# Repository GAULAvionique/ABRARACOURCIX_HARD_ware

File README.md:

# PCB_CTRL_Surface
Le design du hardware qui assurera le contrôle de surface pour le drone prototype.

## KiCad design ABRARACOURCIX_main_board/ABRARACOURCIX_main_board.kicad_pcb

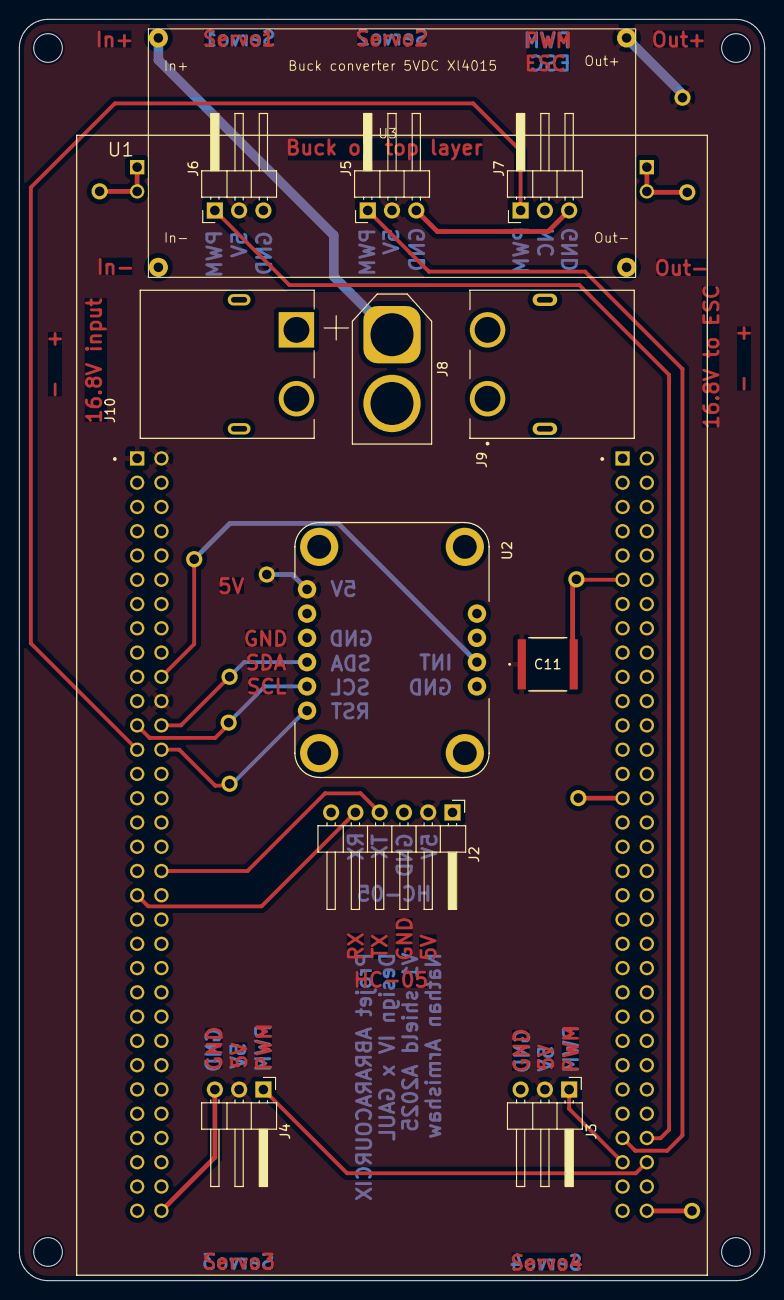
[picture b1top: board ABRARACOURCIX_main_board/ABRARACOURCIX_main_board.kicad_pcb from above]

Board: 2 copper layers, 78.0 x 132.0 mm, 13 parts (0 on the bottom side), 15 nets.

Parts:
C11: 10u; CAP_MU_15750_RUB-L
J2: Conn_01x06_Socket; PinHeader_1x06_P2.54mm_Horizontal
J3, J4, J5, J6, J7: Conn_01x03_Socket; PinHeader_1x03_P2.54mm_Horizontal
J8: XT60PW-M; AMASS_XT60-F_1x02_P7.20mm_Vertical
J9: XT60PW-F; AMASS_XT60PW-F
J10: XT60PW-M; AMASS_XT60PW-M
U1: STM32F429I-DISC1; MODULE_STM32F429I-DISC1
U2: BNO055_breakout; MODULE_2472
U3: Buck_breakout_Xl4015

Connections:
+5V: C11.1, J2.2, J3.2, J4.2, J5.2, J6.2, U1.P1_1 (5V), U1.P1_2 (5V), U1.P1_22 (VDD), U2.1 (VIN), U3.3 (Out+)
/Power/16V_post-switch: J8.1 (+), J9.2, U3.1 (In+)
/Power/16V_pre-switch: J8.2 (-), J10.1 (+)
BNO_Int: U1.P1_20 (PB9), U2.8 (INT)
BNO_Reset: U1.P1_26 (PB5), U2.6 (RST)
GND: C11.2, J2.3, J3.3, J4.3, J5.3, J6.3, J7.3, J9.1, J9.S1 (SHIELD), J9.S2 (SHIELD), J10.2 (-), U1.JP1_1 (GND_1), U1.JP1_2 (GND_1), U1.JP2_1 (GND_2), U1.JP2_2 (GND_2), U1.P1_63 (GND_1), U1.P1_64 (GND_1), U1.P2_11 (GND_2), U1.P2_29 (GND_2), U1.P2_63 (GND_2), U1.P2_64 (GND_2), U2.3 (GND), U2.7 (ADR), U3.2 (In-), U3.4 (Out-)
HC_RX: J2.5, U1.P1_37 (PD5)
HC_TX: J2.4, U1.P1_36 (PD6)
PWM_Moteur: J7.1, U1.P1_25 (PB4)
PWM_Servo_1: J6.1, U1.P2_58 (PD12)
PWM_Servo_2: J5.1, U1.P2_57 (PD13)
PWM_Servo_3: J4.1, U1.P2_60 (PD14)
PWM_Servo_4: J3.1, U1.P2_59 (PD15)
SCL: U1.P1_23 (PB6), U2.5 (SCL)
SDA: U1.P1_24 (PB7), U2.4 (SDA)

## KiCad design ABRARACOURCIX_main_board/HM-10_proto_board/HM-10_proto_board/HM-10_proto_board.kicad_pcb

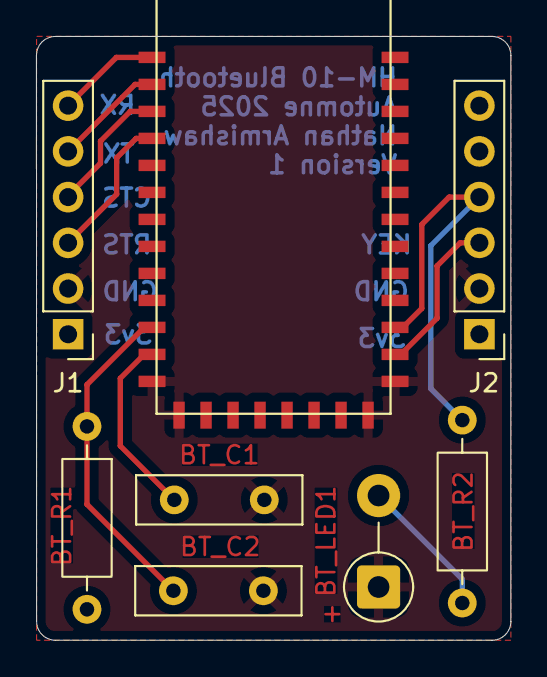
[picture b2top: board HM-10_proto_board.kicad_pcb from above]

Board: 2 copper layers, 26.4 x 33.5 mm, 8 parts (0 on the bottom side), 10 nets.

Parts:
BT_C1: 10uF; C_Disc_D9.0mm_W2.5mm_P5.00mm
BT_C2: 100nF; C_Disc_D9.0mm_W2.5mm_P5.00mm
BT_LED1: BLUE; D_DO-15_P5.08mm_Vertical_AnodeUp
BT_R1: 10k; R_Axial_DIN0207_L6.3mm_D2.5mm_P10.16mm_Horizontal
BT_R2: 1k5; R_Axial_DIN0207_L6.3mm_D2.5mm_P10.16mm_Horizontal
E2: HM-10
J1, J2: Conn_01x06_Socket; PinHeader_1x06_P2.54mm_Vertical

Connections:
+3V3: BT_C1.1, BT_R1.2, E2.12 (+3.3V), J1.1, J2.1
BT_Config/Run: E2.23 (KEY), J2.3
GND: BT_C1.2, BT_C2.2, BT_LED1.1 (K), E2.13 (GND), E2.14 (GND__1), E2.21 (GND__2), E2.22 (GND__3), J1.2, J2.2
unnamed: BT_LED1.2 (A), BT_R2.2
unnamed: BT_R2.1, E2.24 (LED), J2.4
unnamed: BT_C2.1, BT_R1.1, E2.11 (RESET)
UART2_BT_RX: E2.1 (UART_TX), J1.6
UART2_BT_TX: E2.2 (UART_RX), J1.5
UART_CTS: E2.3 (UART_CTS), J1.4
UART_RTS: E2.4 (UART_RTS), J1.3

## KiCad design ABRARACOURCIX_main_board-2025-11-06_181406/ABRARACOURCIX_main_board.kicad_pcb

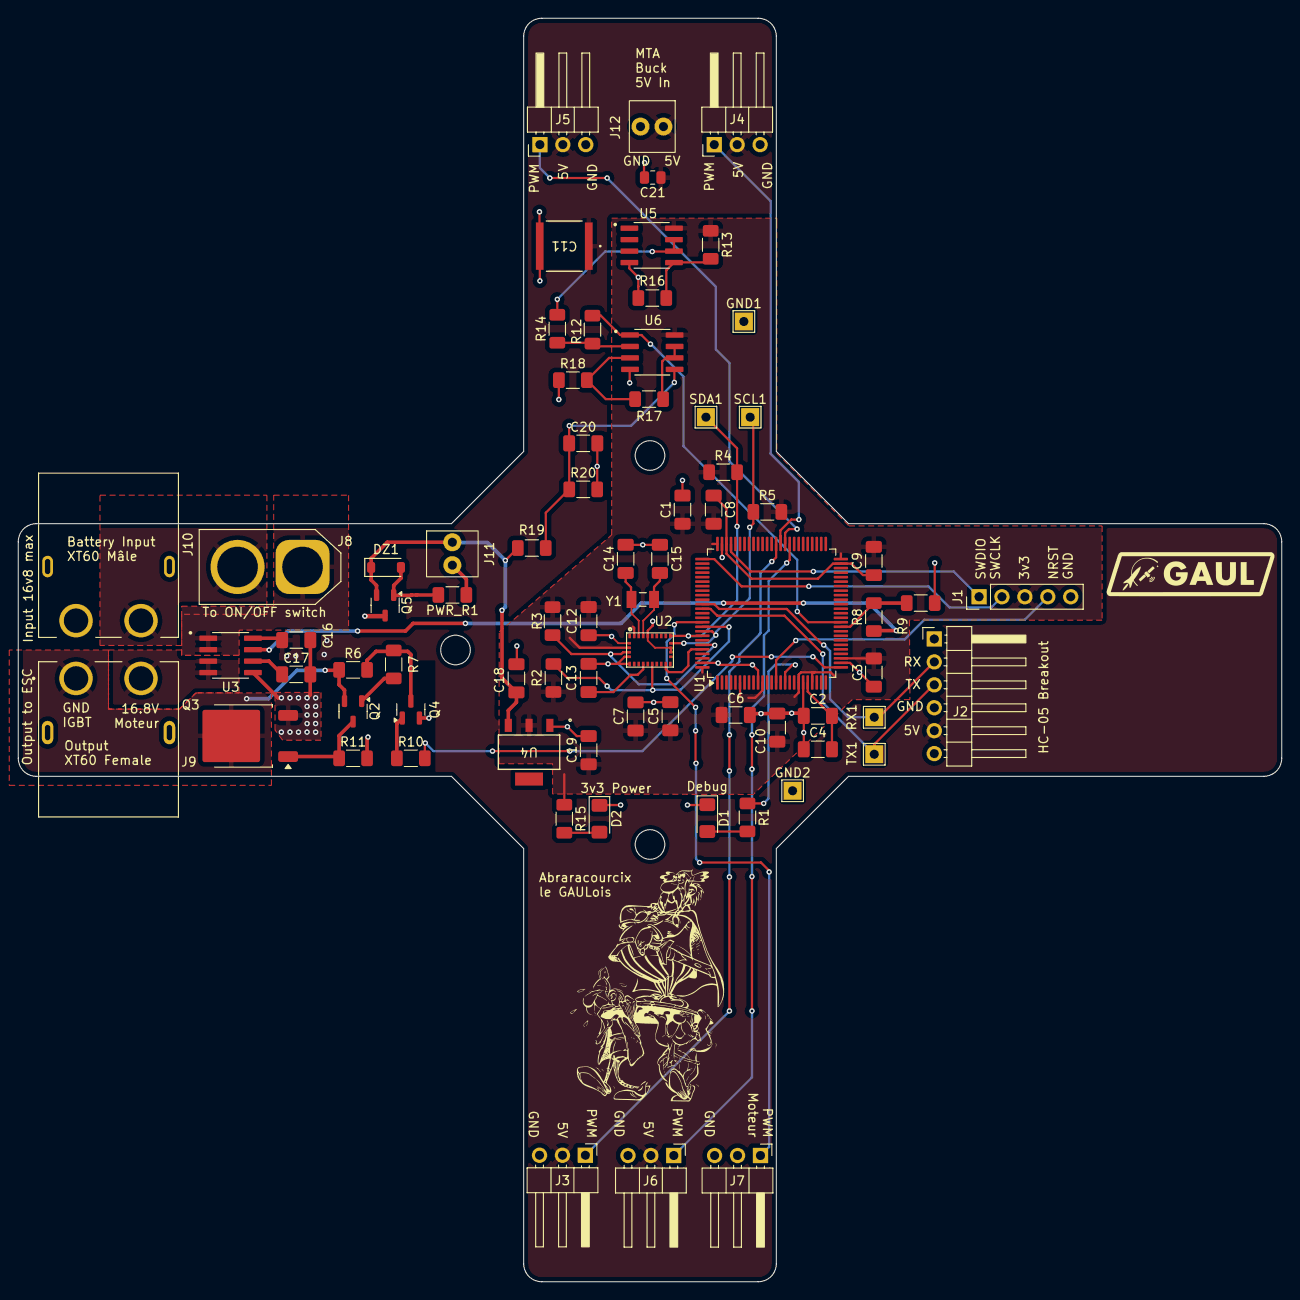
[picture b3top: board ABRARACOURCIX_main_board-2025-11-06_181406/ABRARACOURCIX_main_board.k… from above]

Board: 2 copper layers, 140.0 x 140.0 mm, 75 parts (0 on the bottom side), 47 nets.

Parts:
Abraracourcix_moyen: LOGO; Abraracourcix_moyen
C1, C2, C3, C5, C6: 100n; C_1206_3216Metric_Pad1.33x1.80mm_HandSolder
C4, C10, C20: 1u; C_1206_3216Metric_Pad1.33x1.80mm_HandSolder
C7: 4.7u; C_1206_3216Metric_Pad1.33x1.80mm_HandSolder
C8, C9: 2.2u; C_1206_3216Metric_Pad1.33x1.80mm_HandSolder
C11: 10u; CAP_MU_15750_RUB-L
C12: 100nF; C_1206_3216Metric_Pad1.33x1.80mm_HandSolder
C13: 1uF; C_1206_3216Metric_Pad1.33x1.80mm_HandSolder
C14, C15: 22pF; C_1206_3216Metric_Pad1.33x1.80mm_HandSolder
C16: 0.1u; C_1206_3216Metric_Pad1.33x1.80mm_HandSolder
C17: 1n; C_1206_3216Metric_Pad1.33x1.80mm_HandSolder
C18: 10u; C_1206_3216Metric_Pad1.33x1.80mm_HandSolder
C19: 22u; C_1206_3216Metric_Pad1.33x1.80mm_HandSolder
C21: 22u; R_0805_2012Metric
D1, D2: 599-0410-127F; D_1206_3216Metric_Pad1.42x1.75mm_HandSolder
DZ1: SZMMSZ4679T1G; D_SOD-123
GND1, GND2: TestPoint; TestPoint_THTPad_2.0x2.0mm_Drill1.0mm
J1: Conn_01x05_Socket; PinHeader_1x05_P2.54mm_Vertical
J2: Conn_01x06_Socket; PinHeader_1x06_P2.54mm_Horizontal
J3, J4, J5, J6, J7: Conn_01x03_Socket; PinHeader_1x03_P2.54mm_Horizontal
J8: XT60PW-M; AMASS_XT60-F_1x02_P7.20mm_Vertical
J9: XT60PW-F; AMASS_XT60PW-F
J10: XT60PW-M; AMASS_XT60PW-M
J11, J12: Conn_01x02_Pin; MTA_100_2pos
PWR_R1: 100k; R_1206_3216Metric_Pad1.30x1.75mm_HandSolder
Q2: DSS20200L-7-PNP; SOT-23-3
Q3: IKD15N60R; TO-252-2
Q4: NPN-DSS20201L-7; SOT-23
Q5: NTR4101PT1G; SOT-23-3
R1, R15: 40; R_1206_3216Metric_Pad1.30x1.75mm_HandSolder
R2, R3: 10K; R_1206_3216Metric_Pad1.30x1.75mm_HandSolder
R4: 1K; R_1206_3216Metric_Pad1.30x1.75mm_HandSolder
R5: 1k; R_1206_3216Metric_Pad1.30x1.75mm_HandSolder
R6, R8, R11, R13, R14, R17, R20: 10k; R_1206_3216Metric_Pad1.30x1.75mm_HandSolder
R7, R10: 1k5; R_1206_3216Metric_Pad1.30x1.75mm_HandSolder
R9: 20k; R_1206_3216Metric_Pad1.30x1.75mm_HandSolder
R12, R16, R18: 30k; R_1206_3216Metric_Pad1.30x1.75mm_HandSolder
R19: 40k; R_1206_3216Metric_Pad1.30x1.75mm_HandSolder
RX1: TestPoint; TestPoint_THTPad_2.0x2.0mm_Drill1.0mm
SCL1: TestPoint; TestPoint_THTPad_2.0x2.0mm_Drill1.0mm
SDA1: TestPoint; TestPoint_THTPad_2.0x2.0mm_Drill1.0mm
TX1: TestPoint; TestPoint_THTPad_2.0x2.0mm_Drill1.0mm
U1: STM32F429VITx; LQFP-100_14x14mm_P0.5mm
U2: BNO055; BNO055_LGA28R50P4X10_380X520X100
U3: Current_sens_ACS712ELCTR-20A-T; Current_sens_SOIC127P600X175-8N
U4: AZ1117CH-3.3TRG1; AZ1117CH_3_3TRG1-L
U5, U6: LMC6482AIMX/NOPB; SOIC127P599X175-8N
Y1: ABS07-32.768KHZ-T; XTAL_ABS07-32.768KHZ-T

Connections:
+3.3V: C1.1, C3.1, C5.1, C6.1, C7.1, C8.2, C9.2, C10.1, C12.2, C19.1, J1.3, R2.1, R3.1, R4.1, R5.2, R13.1, R15.1, U1.6 (VBAT), U1.11 (VDD), U1.19 (VDD), U1.22 (VDDA), U1.28 (VDD), U1.50 (VDD), U1.75 (VDD), U1.100 (VDD), U2.3 (VDD), U2.28 (VDDIO), U4.2 (OUTPUT), U5.8 (V+), U6.8 (V+)
+5V: C11.1, C16.1, C21.1, J2.5, J3.2, J4.2, J5.2, J6.2, J12.1, U3.8 (VCC)
/Power/16V_motor: J9.2, Q5.D, U3.3 (IP-__1), U3.4 (IP-)
/Power/16V_post-switch: J8.1 (+), U3.1 (IP+), U3.2 (IP+__1)
/Power/16V_pre-switch: J8.2 (-), J10.1 (+)
/Power/GND_IGBT: J9.1, Q2.E, Q3.C, R6.1
BNO_BOOT: R3.2, U1.95 (PB8), U2.4 (NBOOT_LOAD_PIN)
BNO_INT_OUT: U1.96 (PB9), U2.14 (INT)
BNO_RESET: R2.2, U1.91 (PB5), U2.11 (NRESET)
GND: C1.2, C2.1, C3.2, C4.1, C5.2, C6.2, C7.2, C10.2, C11.2, C12.1, C13.1, C14.2, C15.1, C16.2, C17.2, C18.2, C19.2, C20.2, C21.2, D1.1 (K), D2.1 (K), GND1.1, GND2.1, J1.5, J2.4, J3.3, J4.3, J5.3, J6.3, J7.3, J9.S1 (SHIELD), J9.S2 (SHIELD), J10.2 (-), J11.2, J12.2, PWR_R1.2, Q3.E, Q4.E, R9.2, R11.2, R16.2, R18.1, R20.2, U1.10 (VSS), U1.20 (VSSA), U1.27 (VSS), U1.74 (VSS), U1.99 (VSS), U2.2 (GND), U2.5 (PS1), U2.6 (PS0), U2.17 (COM3), U2.18 (COM2), U2.25 (GNDIO), U3.5 (GND), U4.1 (ADJ/GND), U5.4 (V-), U6.4 (V-)
HC_RX: J2.2, RX1.1, U1.86 (PD5)
HC_TX: J2.3, TX1.1, U1.87 (PD6)
Motor_switch: R10.2, U1.26 (PA3)
NRST: J1.4, U1.14 (NRST)
unnamed: D1.2 (A), R1.2
unnamed: D2.2 (A), R15.2
unnamed: DZ1.2 (A), PWR_R1.1, Q5.G
unnamed: Q2.B, R7.1
unnamed: Q2.C, Q3.G, R11.1
unnamed: Q4.B, R10.1
unnamed: Q4.C, R6.2, R7.2
unnamed: R1.1, U1.16 (PC1)
unnamed: C8.1, C9.1, U1.49 (VCAP_1), U1.73 (VCAP_2)
unnamed: C2.2, C4.2, U1.21 (VREF+)
unnamed: C13.2, U2.9 (CAP)
unnamed: C17.1, U3.6 (FILTER)
unnamed: R8.1, U3.7 (VIOUT)
unnamed: R13.2, R16.1, U5.5 (+)
unnamed: R14.1, U5.6 (-), U5.7
unnamed: R17.2, R18.2, U6.3 (+)
unnamed: R12.1, R14.2, U6.2 (-)
unnamed: C20.1, R19.2, R20.1, U6.5 (+)
unnamed: R17.1, U6.6 (-), U6.7
PWM_Moteur: J7.1, U1.90 (PB4)
PWM_Servo_1: J6.1, U1.59 (PD12)
PWM_Servo_2: J5.1, U1.60 (PD13)
PWM_Servo_3: J4.1, U1.61 (PD14)
PWM_Servo_4: J3.1, U1.62 (PD15)
SCL: R5.1, SCL1.1, U1.92 (PB6), U2.19 (COM1)
SDA: R4.2, SDA1.1, U1.93 (PB7), U2.20 (COM0)
SYS_SWCLK: J1.2, U1.76 (PA14)
SYS_SWDIO: J1.1, U1.72 (PA13)
VBAT_ADC: R12.2, U1.36 (PB1), U6.1
VBAT_sense: C18.1, DZ1.1 (K), J11.1, Q5.S, R19.1, U4.3 (INPUT)
VIout_sense: R8.2, R9.1, U1.35 (PB0)
XIN32: C14.1, U2.27 (XIN32), Y1.2
XOUT32: C15.2, U2.26 (XOUT32), Y1.1

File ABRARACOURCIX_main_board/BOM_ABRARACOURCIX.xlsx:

Reference | Quantity | Order quantity | Value | Footprint | Digikey link | Digikey part number | Description
C11 | 1 | 1 | 10u | Librairie_footprint:CAP_MU_15750_RUB-L | https://www.digikey.ca/en/products/detail/rubycon/16MU106MC4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 | 1189-2511-6-ND | Unpolarized film capacitor
C12 | 1 | 10 | 100nF | Capacitor_SMD:C_1206_3216Metric_Pad1.33x1.80mm_HandSolder | https://www.digikey.ca/en/products/detail/walsin-technology-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 | 1292-1605-1-ND | Unpolarized capacitor
C14, C15 | 2 | 10 | 22pF | Capacitor_SMD:C_1206_3216Metric_Pad1.33x1.80mm_HandSolder | https://www.digikey.ca/en/products/detail/kemet/C1206C220K1G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 | 399-C1206C220K1GACTUCT-ND | Unpolarized capacitor
C17 | 1 | 10 | 1n | Capacitor_SMD:C_1206_3216Metric_Pad1.33x1.80mm_HandSolder | https://www.digikey.ca/en/products/detail/walsin-technology-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 | 1292-1598-1-ND | Unpolarized capacitor
C18 | 1 | 10 | 10u | Capacitor_SMD:C_1206_3216Metric_Pad1.33x1.80mm_HandSolder | https://www.digikey.ca/en/products/detail/walsin-technology-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 | 1292-1206X106K250CT-ND | Unpolarized capacitor
C19, C21 | 2 | 10 | 22u | Capacitor_SMD:C_1206_3216Metric_Pad1.33x1.80mm_HandSolder | https://www.digikey.ca/en/products/detail/walsin-technology-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 | 1292-1206X226M160CT-ND | Unpolarized capacitor
C1-C3, C5, C6, C16 | 6 | 10 | 100n | Capacitor_SMD:C_1206_3216Metric_Pad1.33x1.80mm_HandSolder | Link | 1292-1605-1-ND | Unpolarized capacitor
C4, C10, C13, C20 | 4 | 10 | 1u | Capacitor_SMD:C_1206_3216Metric_Pad1.33x1.80mm_HandSolder | https://www.digikey.ca/en/products/detail/walsin-technology-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 | 1292-1206B105K250CT-ND | Unpolarized capacitor
C7 | 1 | 10 | 4.7u | Capacitor_SMD:C_1206_3216Metric_Pad1.33x1.80mm_HandSolder | https://www.digikey.ca/en/products/detail/walsin-technology-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 | 1292-1206B475K250CT-ND | Unpolarized capacitor
C8, C9 | 2 | 10 | 2.2u | Capacitor_SMD:C_1206_3216Metric_Pad1.33x1.80mm_HandSolder | https://www.digikey.ca/en/products/detail/walsin-technology-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 | 1292-1206B225K250CT-ND | Unpolarized capacitor
D1, D2 | 2 | 10 | 599-0410-127F | Diode_SMD:D_1206_3216Metric_Pad1.42x1.75mm_HandSolder | https://www.digikey.ca/en/products/detail/dialight/599-0410-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 | 350-599-0410-127FCT-ND | Light emitting diode
DZ1 | 1 | 10 | SZMMSZ4679T1G | Diode_SMD:D_SOD-123 | https://www.digikey.ca/en/products/detail/onsemi/SZMMSZ4679T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 | SZMMSZ4679T1GOSCT-ND | 18V, 500mW, 5%, Zener diode, MiniMELF
J1 | 1 | 2 | Conn_01x05_Socket | Connector_PinHeader_2.54mm:PinHeader_1x05_P2.54mm_Vertical | https://www.digikey.ca/en/products/detail/sullins-connector-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 | S5480-ND | CONN HDR 5POS 0.1 GOLD PCB R/A
J2 | 1 | 2 | Conn_01x06_Socket | Connector_PinHeader_2.54mm:PinHeader_1x06_P2.54mm_Horizontal | https://www.digikey.ca/en/products/detail/samtec-inc/SSW-106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 | SSW-106-03-F-S-RA-ND | Generic connector, single row, 01x06, script generated
J3-J7 | 5 | 5 | Conn_01x03_Socket | Connector_PinHeader_2.54mm:PinHeader_1x03_P2.54mm_Horizontal | https://www.digikey.ca/en/products/detail/harwin-inc/M20-996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 | M20-9960345 | Generic connector, single row, 01x03, script generated
PWR_R1 | 1 | 2 | 100k | Resistor_SMD:R_1206_3216Metric_Pad1.30x1.75mm_HandSolder | https://www.digikey.ca/en/products/detail/bourns-inc/CR1206-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 | CR1206-JW-104ELFCT-ND | RES SMD 100K OHM 5% 1/4W 1206
Q2 | 1 | 3 | DSS20200L-7-PNP | Package_TO_SOT_SMD:SOT-23-3 | https://www.digikey.ca/en/products/detail/diodes-incorporate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 | DSS20200LDICT-ND | Bipolar transistor symbol for simulation only, substrate tied to the emitter
Q3 | 1 | 2 | IKD15N60R | Package_TO_SOT_SMD:TO-252-2 | https://www.digikey.ca/en/products/detail/infineon-technolog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 | NTR4101PT1GOSCT-ND | N-IGBT transistor, collector/emitter/gate
Q4 | 1 | 3 | NPN-DSS20201L-7 | Package_TO_SOT_SMD:SOT-23 | https://www.digikey.ca/en/products/detail/diodes-incorporate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 | DSS20201LDICT-ND | Bipolar transistor symbol for simulation only, substrate tied to the emitter
Q5 | 1 | 3 | NTR4101PT1G | Package_TO_SOT_SMD:SOT-23-3 | https://www.digikey.ca/en/products/detail/onsemi/NTR4101PT1G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 | NTR4101PT1GOSCT-ND | P-MOSFET transistor, drain/source/gate
R1, R15 | 2 | 10 | 40.2 | Resistor_SMD:R_1206_3216Metric_Pad1.30x1.75mm_HandSolder | https://www.digikey.ca/en/products/detail/bourns-inc/CR1206-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 | 118-CR1206-FX-40R2ELFCT-ND | Resistor
R12, R16, R18 | 3 | 10 | 30k | Resistor_SMD:R_1206_3216Metric_Pad1.30x1.75mm_HandSolder | https://www.digikey.ca/en/products/detail/bourns-inc/CR1206-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 | 118-CR1206-JW-303ELFCT-ND | Resistor
R19 | 1 | 10 | 40.2k | Resistor_SMD:R_1206_3216Metric_Pad1.30x1.75mm_HandSolder | https://www.digikey.ca/en/products/detail/bourns-inc/CR1206-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 | 118-CR1206-FX-4022ELFCT-ND | Resistor
R2, R3 | 2 | 10 | 10K | Resistor_SMD:R_1206_3216Metric_Pad1.30x1.75mm_HandSolder | https://www.digikey.ca/en/products/detail/bourns-inc/CR1206-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 | CR1206-JW-103ELFCT-ND | Resistor
R4 | 1 | 10 | 1K | Resistor_SMD:R_1206_3216Metric_Pad1.30x1.75mm_HandSolder | https://www.digikey.ca/en/products/detail/bourns-inc/CR1206-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 | 118-CR1206-JW-102ELFCT-ND | Resistor
R5 | 1 | 10 | 1k | Resistor_SMD:R_1206_3216Metric_Pad1.30x1.75mm_HandSolder | https://www.digikey.ca/en/products/detail/bourns-inc/CR1206-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 | 118-CR1206-JW-102ELFCT-ND | Resistor
R6, R8, R11, R13, R14, R17, R20 | 7 | 10 | 10k | Resistor_SMD:R_1206_3216Metric_Pad1.30x1.75mm_HandSolder | https://www.digikey.ca/en/products/detail/bourns-inc/CR1206-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 | CR1206-JW-103ELFCT-ND | Resistor
R7, R10 | 2 | 10 | 1k5 | Resistor_SMD:R_1206_3216Metric_Pad1.30x1.75mm_HandSolder | https://www.digikey.ca/en/products/detail/bourns-inc/CR1206-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 | CR1206-JW-152ELFCT-ND | Resistor
R9 | 1 | 10 | 20k | Resistor_SMD:R_1206_3216Metric_Pad1.30x1.75mm_HandSolder | https://www.digikey.ca/en/products/detail/bourns-inc/CR1206-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 | 118-CR1206-JW-203ELFCT-ND | RES SMD 20K OHM 5% 1/4W 1206
U1 | 1 | 2 | STM32F429VITx | Package_QFP:LQFP-100_14x14mm_P0.5mm | https://www.digikey.ca/en/products/detail/stmicroelectronics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 | 497-14052-ND | STMicroelectronics Arm Cortex-M4 MCU, 2048KB flash, 256KB RAM, 180 MHz, 1.8-3.6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
U2 | 1 | 2 | BNO055 | Librairie_footprint:BNO055_LGA28R50P4X10_380X520X100 | https://www.digikey.ca/en/products/detail/bosch-sensortec/BN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 | 828-1058-1-ND | Inertial Measurement Unit
U3 | 1 | 2 | Current_sens_ACS712ELCTR-20A-T | Librairie_footprint:Current_sens_SOIC127P600X175-8N | https://www.digikey.ca/en/products/detail/allegro-microsyste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 | 620-1190-1-ND | CURRENT SENSOR HE/OL 20A 8-SOIC
U4 | 1 | 10 | AZ1117CH-3.3TRG1 | Librairie_footprint:AZ1117CH_3_3TRG1-L | https://www.digikey.ca/en/products/detail/diodes-incorporate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 | AZ1117CH-3.3TRG1DICT-ND | 3v3 LDO
U5, U6 | 2 | 2 | LMC6482AIMX/NOPB | Librairie_footprint:SOIC127P599X175-8N | https://www.digikey.ca/en/products/detail/texas-instruments/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 | LMC6482AIMX/NOPBCT-ND | IC CMOS 2 CIRCUIT 8SOIC
Y1 | 1 | 2 | ABS07-32.768KHZ-T | Librairie_footprint:XTAL_ABS07-32.768KHZ-T | https://www.digikey.ca/en/products/detail/abracon-llc/ABS07-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 | 535-9542-1-ND | CRYSTAL 32.7680KHZ 12.5PF SMD

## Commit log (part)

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2025-09-05 Création des docs
2025-09-05 schema bloc
2025-09-06 Update au schema bloc
2025-09-10 Importation des librairies
    Librairies des composantes principales
    Reste à ajouter l'IO
2025-09-11 Terminé les interconnects
    Toutes les interfaces et le power sont terminés. (À vérifier)
    Reste à ajouter toutes les connexions au ICM et stm32
2025-09-12 Avancement
    Decoupling caps
    Changement de stm32
2025-09-23 Commit de kicad
2025-09-23 commit de git
2025-09-26 Changements obsolete
2025-09-26 Création d'un board pour le HM10
2025-09-26 Avancement
    Commencer à relier le stm32
2025-10-03 autosave
2025-10-03 Commit le stash
2025-10-03 Correction des erreurs de merge dans branche Nathan
2025-10-03 Resolution du stash
2025-10-03 Correction du schematic
2025-10-03 Correction du fichier pcb
2025-10-21 Damn j'ai oublié de push y'a 2 semaines
    je sais plus
2025-10-31 Reprise de contrôle
    Schematics terminés
    Reste à associer des composantes et vérification
2025-11-06 Modif lecture tension
2025-11-06 Assignation d<empreintes terminée
2025-11-10 modifs pas importantes
2025-11-10 début pcb
2025-11-11 Modifs au circuit d'alim
2025-11-11 Modif circuit d'arrêt
2025-11-11 Placement des composantes 95%
2025-11-12 Documentation de composantes
2025-11-13 Déplacement des mounting holes et début du routing
2025-11-13 Avancement routing section power
2025-11-14 Routing terminé (v1)
2025-11-16 Ajout de dessins et info silkscreen
2025-11-16 Recommencer assignation des composantes
2025-11-19 Host_modification
2025-11-20 Documentation, lien digikey et part number assigné à toutes les composantes
2025-12-01 Circuit+début PCB
2025-12-01 PCB terminé
2025-12-01 Fichiers de fabrication
2025-12-01 Ajustement des gerbers
2025-12-05 Liste des modifs pour la V2
2025-12-08 plus d'erreur
2025-12-08 Notes d'améliorations
2025-12-13 Je sais plus
